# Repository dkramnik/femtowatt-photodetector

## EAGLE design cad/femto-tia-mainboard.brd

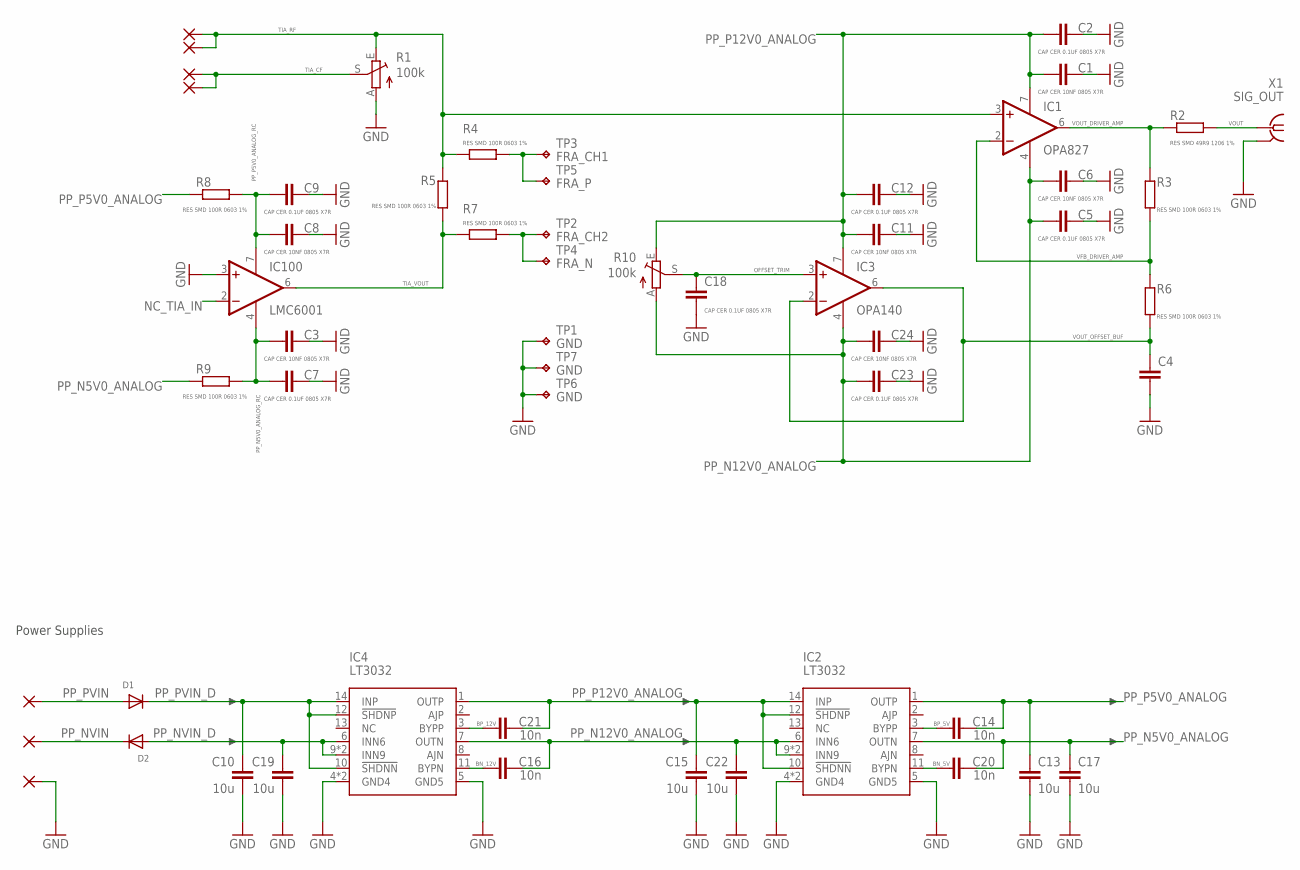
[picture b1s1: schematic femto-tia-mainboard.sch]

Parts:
C1, C3, C6, C8, C11, C24: CAP CER 10NF 0805 X7R; C0805
C2, C5, C7, C9, C12, C18, C23: CAP CER 0.1UF 0805 X7R; C0805
C4: C-EUC0805; C0805
C10, C13, C15, C17, C19, C22: 10u; C1206
C14, C16, C20, C21: 10n; C0603
D1, D2: DIODESMA; SMADIODE
IC1: OPA827; SO08
IC2, IC4: LT3032; DFN14-4X3DE
IC3: OPA140; SO08
IC100: LMC6001; DIL08
R1, R10: 100k; RJ9W
R2: RES SMD 49R9 1206 1%; R1206
R3, R4, R5, R6, R7, R8, R9: RES SMD 100R 0603 1%; R0805
TP1, TP6, TP7: GND; KEYSTONE_5000_MINIATURE
TP2: FRA_CH2; KEYSTONE_5000_MINIATURE
TP3: FRA_CH1; KEYSTONE_5000_MINIATURE
TP4: FRA_N; KEYSTONE_5000_MINIATURE
TP5: FRA_P; KEYSTONE_5000_MINIATURE
U$1, U$2, U$3: VIA
U$4: RF; VIA
U$5: GND; VIA
U$6: IN+; VIA
U$7: IN-; VIA
X1: SIG_OUT; J502-ND-142-0701-881/886

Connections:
BN_5V: C20.1, IC2.11 (BYPN)
BN_12V: C16.1, IC4.11 (BYPN)
BP_5V: C14.1, IC2.3 (BYPP)
BP_12V: C21.1, IC4.3 (BYPP)
GND: C1.2, C2.2, C3.2, C4.2, C5.2, C6.2, C7.2, C8.2, C9.2, C10.2, C11.2, C12.2, C13.2, C15.2, C17.2, C18.2, C19.2, C22.2, C23.2, C24.2, IC2.4 (GND4), IC2.4_PAD (GND4), IC4.4 (GND4), IC4.4_PAD (GND4), IC100.3 (+IN), R1.A, TP1.P$1, TP6.P$1, TP7.P$1, U$5.1, X1.G@1 (GND), X1.G@2 (GND), X1.G@3 (GND), X1.G@4 (GND)
unnamed: R7.2, TP2.P$1, TP4.P$1
unnamed: R4.2, TP3.P$1, TP5.P$1
NC_TIA_IN: IC100.2 (-IN)
OFFSET_TRIM: C18.1, IC3.3 (+IN), R10.S
PP_N5V0_ANALOG: C17.1, C20.2, IC2.7 (OUTN), R9.2
PP_N5V0_ANALOG_RC: C3.1, C7.1, IC100.4 (V-), R9.1
PP_N12V0_ANALOG: C5.1, C6.1, C16.2, C22.1, C23.1, C24.1, IC1.4 (V-), IC2.6 (INN6), IC2.9 (INN9), IC2.9_PAD (INN9), IC3.4 (V-), IC4.7 (OUTN), R10.A
PP_NVIN: D2.C, U$7.1
PP_NVIN_D: C19.1, D2.A, IC4.6 (INN6), IC4.9 (INN9), IC4.9_PAD (INN9)
PP_P5V0_ANALOG: C13.1, C14.2, IC2.1 (OUTP), R8.2
PP_P5V0_ANALOG_RC: C8.1, C9.1, IC100.7 (V+), R8.1
PP_P12V0_ANALOG: C1.1, C2.1, C11.1, C12.1, C15.1, C21.2, IC1.7 (V+), IC2.10 (!SHDNN), IC2.12 (!SHDNP), IC2.14 (INP), IC3.7 (V+), IC4.1 (OUTP), R10.E
PP_PVIN: D1.A, U$6.1
PP_PVIN_D: C10.1, D1.C, IC4.10 (!SHDNN), IC4.12 (!SHDNP), IC4.14 (INP)
TIA_CF: R1.S, U$1.1, U$2.1
TIA_RF: IC1.3 (+IN), R1.E, R4.1, R5.1, U$3.1, U$4.1
TIA_VOUT: IC100.6 (OUT), R5.2, R7.1
VFB_DRIVER_AMP: IC1.2 (-IN), R3.1, R6.2
VOUT: R2.2, X1.1
VOUT_DRIVER_AMP: IC1.6 (OUT), R2.1, R3.2
VOUT_OFFSET_BUF: C4.1, IC3.2 (-IN), IC3.6 (OUT), R6.1

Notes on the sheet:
Power Supplies

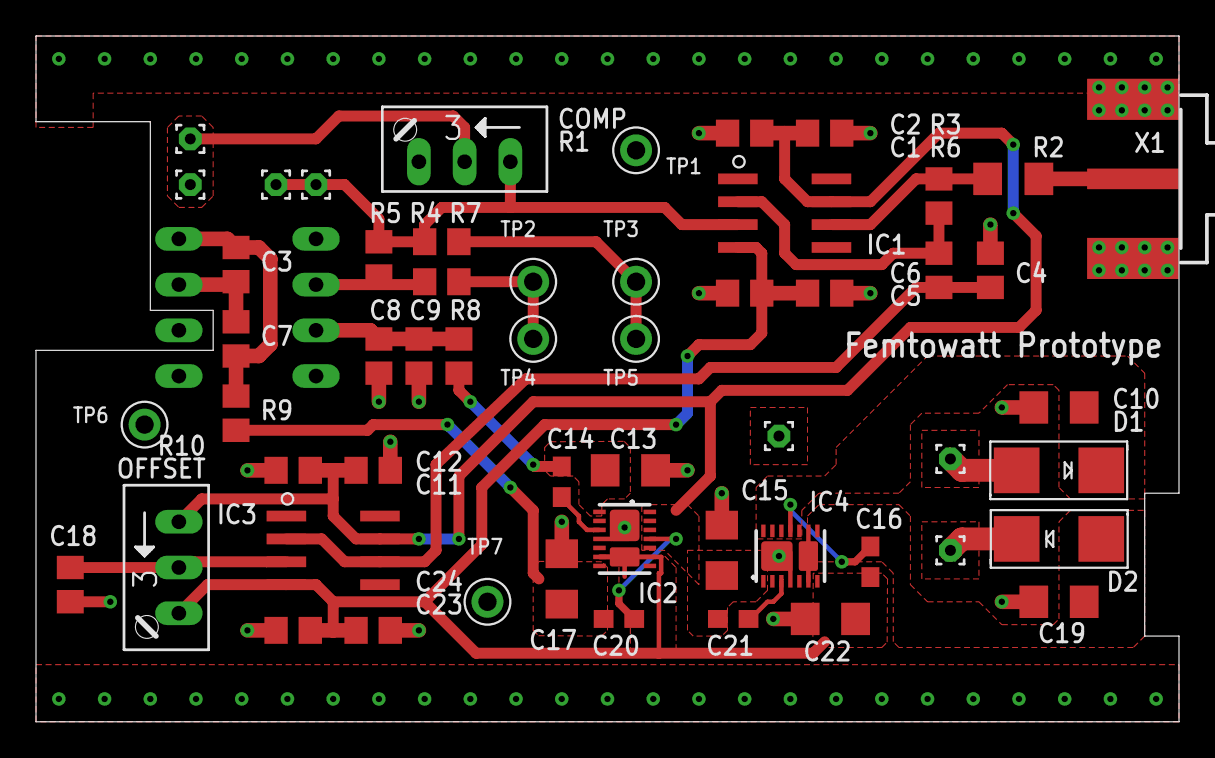
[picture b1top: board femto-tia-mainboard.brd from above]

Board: 2 copper layers, 63.5 x 38.1 mm, 56 parts (1 on the bottom side), 25 nets.

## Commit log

2020-07-10 Started project
2020-07-16 Added some refs and basic design script
2020-07-23 Added ref
2020-08-02 Misc simulation setup
2020-08-03 Added gitignore, worked on schematic and initial placement
2020-08-03 Added some simple loop gain calcs
2020-08-07 More layout, close to done
2020-08-10 Done with first-pass routing
2020-08-11 Added more vars to mat save
2020-08-13 Added ohmite datasheet
2020-08-14 Exported gerbers and sent out first prototype
